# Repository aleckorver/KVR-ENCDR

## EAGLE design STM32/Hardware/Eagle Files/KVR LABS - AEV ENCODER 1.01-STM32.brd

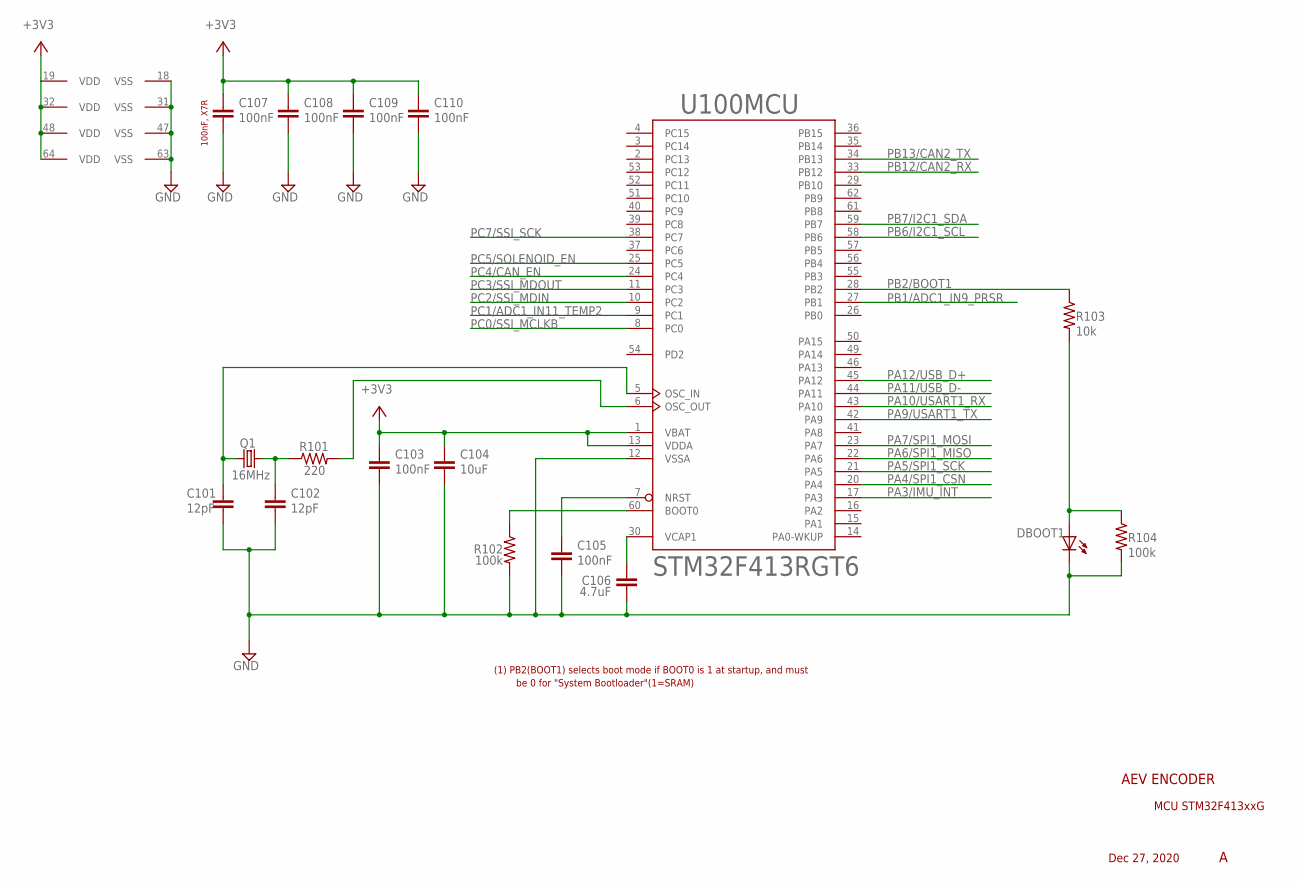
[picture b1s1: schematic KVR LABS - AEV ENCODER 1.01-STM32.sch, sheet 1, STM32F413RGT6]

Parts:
C101, C102: 12pF; C0603
C103, C105, C107, C108, C109, C110: 100nF; C0603
C104: 10uF; C0603
C106: 4.7uF; C0603
DBOOT1: LEDCHIPLED_0805; CHIPLED_0805
Q1: 16MHz; CRY3225-4
R101: 220; R0603
R102, R104: 100k; R0603
R103: 10k; R0603
U100: STM32F413RGT6; LQFP64_STMLIB

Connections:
+3V3: C103.1, C104.1, C107.1, C108.1, C109.1, C110.1, U100.1 (VBAT), U100.13 (VDDA), U100.19 (VDD), U100.32 (VDD), U100.48 (VDD), U100.64 (VDD); also elsewhere on the board
BOOT0: R102.1, U100.60 (BOOT0); also elsewhere on the board
GND: C101.2, C102.2, C103.2, C104.2, C105.2, C106.2, C107.2, C108.2, C109.2, C110.2, DBOOT1.C, R102.2, R104.2, U100.12 (VSSA), U100.18 (VSS), U100.31 (VSS), U100.47 (VSS), U100.63 (VSS); also elsewhere on the board
unnamed: DBOOT1.A, R103.2, R104.1
unnamed: R101.2, U100.6 (OSC_OUT)
NRST: C105.1, U100.7 (NRST)
OSC_IN: C101.1, Q1.3 (2), U100.5 (OSC_IN)
OSC_OUT: C102.1, Q1.1, R101.1
PA3/IMU_INT: U100.17 (PA3); also elsewhere on the board
PA4/SPI1_CSN: U100.20 (PA4); also elsewhere on the board
PA5/SPI1_SCK: U100.21 (PA5); also elsewhere on the board
PA6/SPI1_MISO: U100.22 (PA6); also elsewhere on the board
PA7/SPI1_MOSI: U100.23 (PA7); also elsewhere on the board
PA9/USART1_TX: U100.42 (PA9); also elsewhere on the board
PA10/USART1_RX: U100.43 (PA10); also elsewhere on the board
PA11/USB_D-: U100.44 (PA11); also elsewhere on the board
PA12/USB_D+: U100.45 (PA12); also elsewhere on the board
PB1/ADC1_IN9_PRSR: U100.27 (PB1); also elsewhere on the board
PB2/BOOT1: R103.1, U100.28 (PB2); also elsewhere on the board
PB6/I2C1_SCL: U100.58 (PB6)
PB7/I2C1_SDA: U100.59 (PB7)
PB12/CAN2_RX: U100.33 (PB12); also elsewhere on the board
PB13/CAN2_TX: U100.34 (PB13); also elsewhere on the board
PC0/SSI_MCLKB: U100.8 (PC0); also elsewhere on the board
PC1/ADC1_IN11_TEMP2: U100.9 (PC1); also elsewhere on the board
PC2/SSI_MDIN: U100.10 (PC2); also elsewhere on the board
PC3/SSI_MDOUT: U100.11 (PC3); also elsewhere on the board
PC4/CAN_EN: U100.24 (PC4); also elsewhere on the board
PC5/SOLENOID_EN: U100.25 (PC5); also elsewhere on the board
PC7/SSI_SCK: U100.38 (PC7); also elsewhere on the board
VCAP: C106.1, U100.30 (VCAP1)

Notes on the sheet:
AEV ENCODER
MCU STM32F413xxG
Dec 27, 2020
100nF, X7R
(1) PB2(BOOT1) selects boot mode if BOOT0 is 1 at startup, and must
be 0 for "System Bootloader"(1=SRAM)

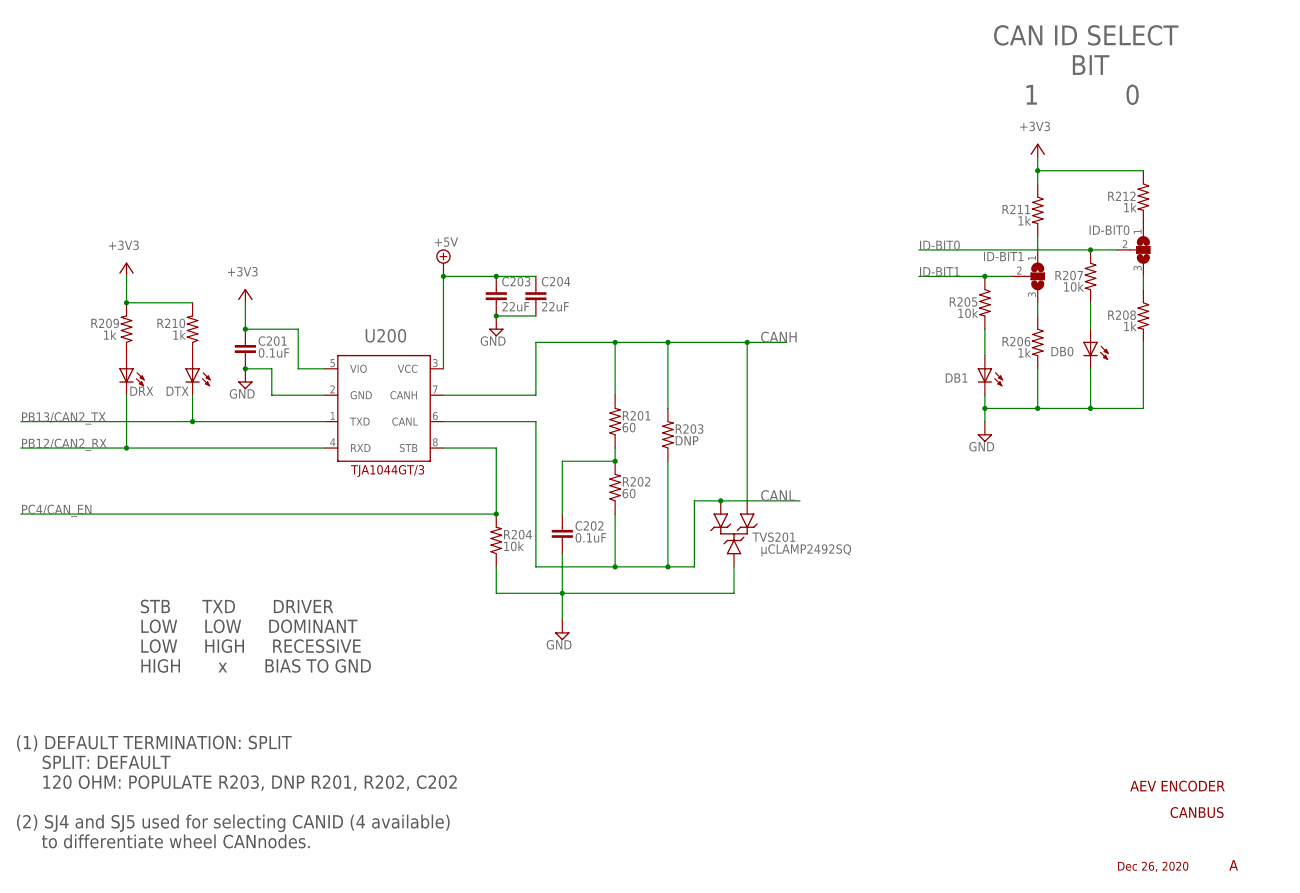
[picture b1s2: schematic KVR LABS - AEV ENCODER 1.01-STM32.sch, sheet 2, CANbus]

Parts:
C201, C202: 0.1uF; C0603
C203, C204: 22uF; C1206
D201: μCLAMP2492SQ; SOT-23_3L_ONS
DB0, DB1: LEDCHIPLED_0805; CHIPLED_0805
DRX: LEDCHIPLED_0805; CHIPLED_0805
DTX: LEDCHIPLED_0805; CHIPLED_0805
ID-BIT0, ID-BIT1: SJ2W; SJ_2
R201, R202: 60; R0603
R203: DNP; R0603
R204, R205, R207: 10k; R0603
R206, R208, R209, R210, R211, R212: 1k; R0603
U200: TJA1044GT/3; SO-8_S_LIT

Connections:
+3V3: C201.1, R209.2, R210.2, R211.1, R212.1, U200.5 (VIO); also elsewhere on the board
+5V: C203.1, C204.1, U200.3 (VCC); also elsewhere on the board
CANH: D201.2, R201.2, R203.2, U200.7 (CANH); also elsewhere on the board
CANL: D201.1, R202.1, R203.1, U200.6 (CANL); also elsewhere on the board
GND: C201.2, C202.2, C203.2, C204.2, D201.3, DB0.C, DB1.C, R204.1, R206.2, R208.2, U200.2 (GND); also elsewhere on the board
ID-BIT0: ID-BIT0.2, R207.1
ID-BIT1: ID-BIT1.2, R205.1
unnamed: ID-BIT1.3, R206.1
unnamed: ID-BIT0.3, R208.1
unnamed: DB0.A, R207.2
unnamed: DB1.A, R205.2
unnamed: ID-BIT1.1, R211.2
unnamed: ID-BIT0.1, R212.2
unnamed: DRX.A, R209.1
unnamed: DTX.A, R210.1
PB12/CAN2_RX: DRX.C, U200.4 (RXD); also elsewhere on the board
PB13/CAN2_TX: DTX.C, U200.1 (TXD); also elsewhere on the board
PC4/CAN_EN: R204.2, U200.8 (STB); also elsewhere on the board
SPLIT: C202.1, R201.1, R202.2

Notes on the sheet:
CANBUS
AEV ENCODER
Dec 26, 2020
(1) DEFAULT TERMINATION: SPLIT SPLIT: DEFAULT 120 OHM: POPULATE R203, DNP R201, R202, C202 (2) SJ4 and SJ5 used for selecting CANID (4 available) to differentiate wheel CANnodes.
CAN ID SELECT BIT 1 0
TVS201
U200
STB TXD DRIVER LOW LOW DOMINANT LOW HIGH RECESSIVE HIGH x BIAS TO GND

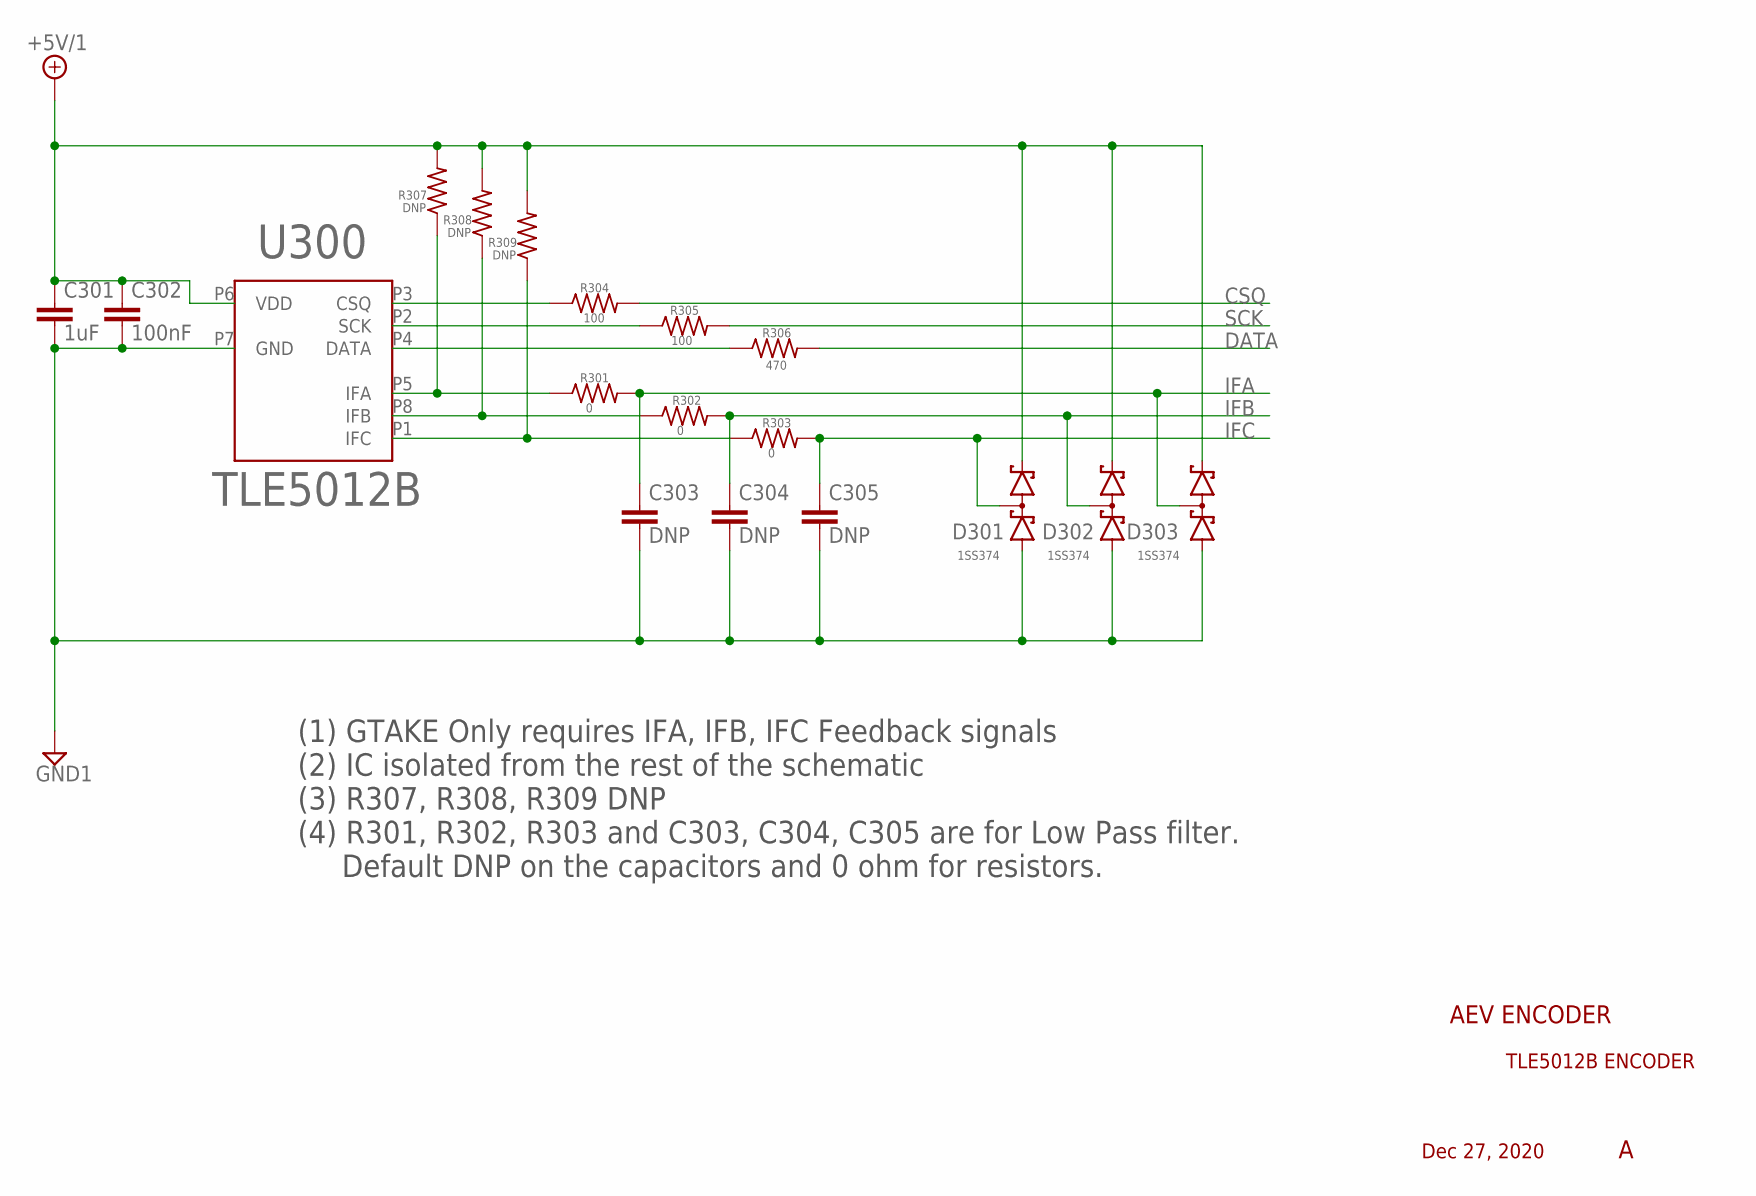
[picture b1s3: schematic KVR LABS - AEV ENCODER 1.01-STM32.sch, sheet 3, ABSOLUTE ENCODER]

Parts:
C301: 1uF; C0603
C302: 100nF; C0603
C303, C304, C305: DNP; C0603
D301, D302, D303: BAS70-04; SOT23
R301, R302, R303: 0; R0603
R304, R305: 100; R0603
R306: 470; R0603
R307, R308, R309: DNP; R0603
U300: TLE5012B; PG-DSO-8

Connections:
+5V/1: C301.1, C302.1, D301.2 (C2), D302.2 (C2), D303.2 (C2), R307.2, R308.2, R309.2, U300.P6 (VDD); also elsewhere on the board
CSQ: R304.2; also elsewhere on the board
DATA: R306.2; also elsewhere on the board
GND1: C301.2, C302.2, C303.2, C304.2, C305.2, D301.1 (A1), D302.1 (A1), D303.1 (A1), U300.P7 (GND); also elsewhere on the board
IFA: C303.1, D303.3 (C1A2), R301.2; also elsewhere on the board
IFB: C304.1, D302.3 (C1A2), R302.2; also elsewhere on the board
IFC: C305.1, D301.3 (C1A2), R303.2; also elsewhere on the board
unnamed: R304.1, U300.P3 (CSQ)
unnamed: R305.1, U300.P2 (SCK)
unnamed: R306.1, U300.P4 (DATA)
unnamed: R301.1, R307.1, U300.P5 (IFA)
unnamed: R302.1, R308.1, U300.P8 (IFB)
unnamed: R303.1, R309.1, U300.P1 (IFC)
SCK: R305.2; also elsewhere on the board

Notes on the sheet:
AEV ENCODER
TLE5012B ENCODER
Dec 27, 2020
U300
(1) GTAKE Only requires IFA, IFB, IFC Feedback signals (2) IC isolated from the rest of the schematic (3) R307, R308, R309 DNP (4) R301, R302, R303 and C303, C304, C305 are for Low Pass filter. Default DNP on the capacitors and 0 ohm for resistors.

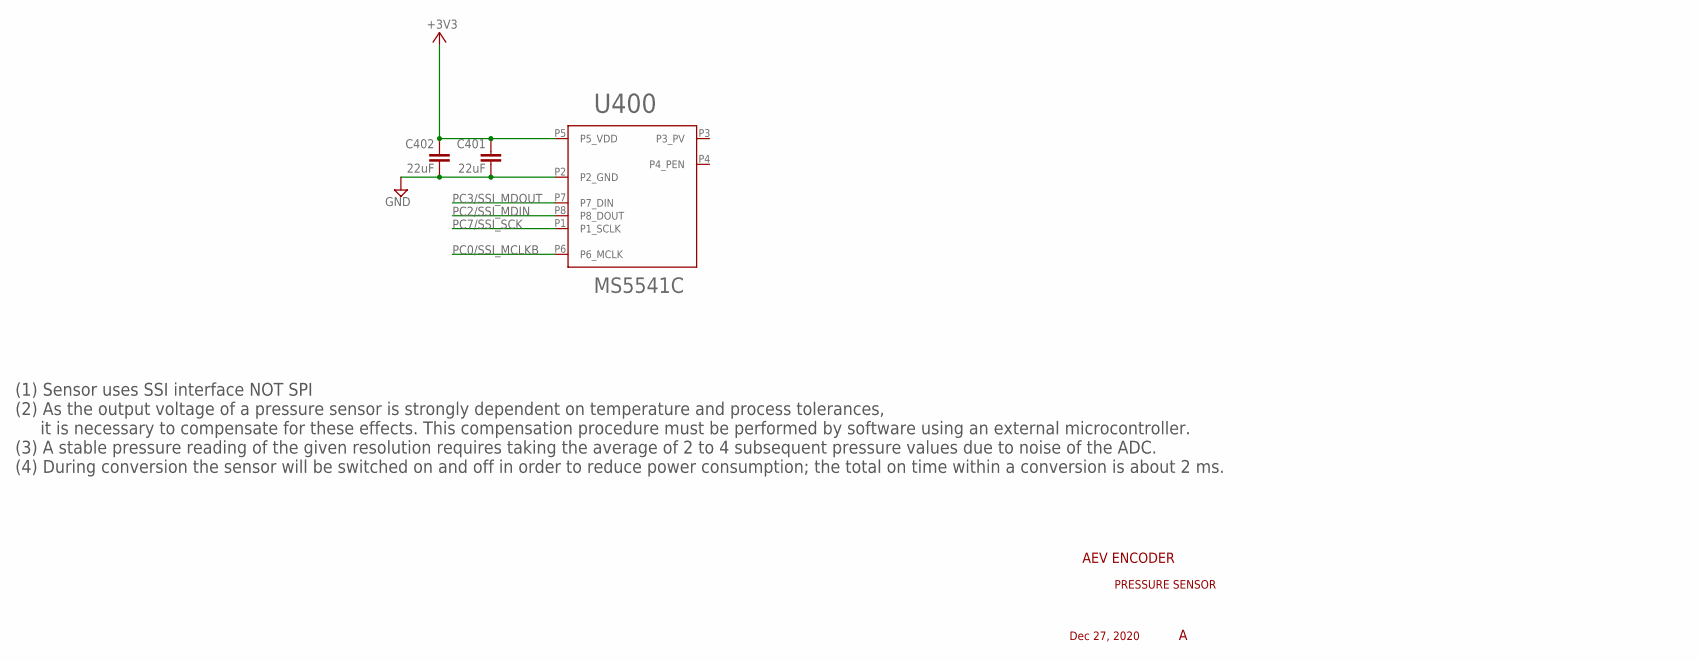
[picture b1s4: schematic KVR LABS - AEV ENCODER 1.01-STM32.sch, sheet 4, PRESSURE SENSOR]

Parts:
C401, C402: 22uF; C1206
U400: MS5541C

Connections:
+3V3: C401.1, C402.1, U400.P5 (P5_VDD); also elsewhere on the board
GND: C401.2, C402.2, U400.P2 (P2_GND); also elsewhere on the board
PC0/SSI_MCLKB: U400.P6 (P6_MCLK); also elsewhere on the board
PC2/SSI_MDIN: U400.P8 (P8_DOUT); also elsewhere on the board
PC3/SSI_MDOUT: U400.P7 (P7_DIN); also elsewhere on the board
PC7/SSI_SCK: U400.P1 (P1_SCLK); also elsewhere on the board

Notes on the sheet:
AEV ENCODER
PRESSURE SENSOR
Dec 27, 2020
(1) Sensor uses SSI interface NOT SPI (2) As the output voltage of a pressure sensor is strongly dependent on temperature and process tolerances, it is necessary to compensate for these effects. This compensation procedure must be performed by software using an external microcontroller. (3) A stabl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

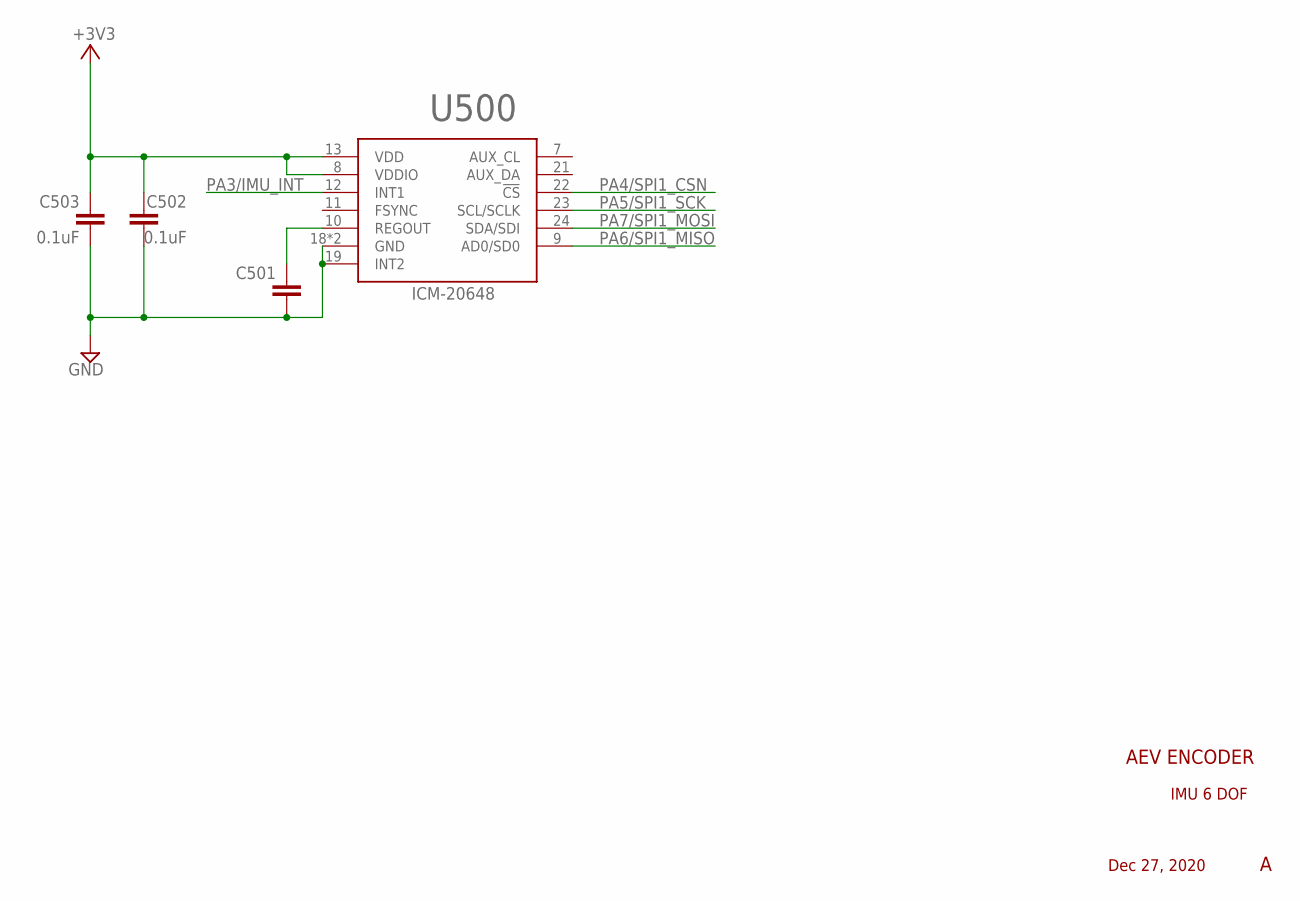
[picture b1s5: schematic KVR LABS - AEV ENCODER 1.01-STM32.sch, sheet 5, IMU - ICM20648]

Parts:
C501, C502, C503: 0.1uF; C0603
U500: ICM-20648

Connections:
+3V3: C502.1, C503.1, U500.8 (VDDIO), U500.13 (VDD); also elsewhere on the board
GND: C501.2, C502.2, C503.2, U500.18 (GND), U500.19 (INT2), U500.20 (GND); also elsewhere on the board
PA3/IMU_INT: U500.12 (INT1); also elsewhere on the board
PA4/SPI1_CSN: U500.22 (!CS); also elsewhere on the board
PA5/SPI1_SCK: U500.23 (SCL/SCLK); also elsewhere on the board
PA6/SPI1_MISO: U500.9 (AD0/SD0); also elsewhere on the board
PA7/SPI1_MOSI: U500.24 (SDA/SDI); also elsewhere on the board
REGOUT2: C501.1, U500.10 (REGOUT)

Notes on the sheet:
AEV ENCODER
IMU 6 DOF
Dec 27, 2020

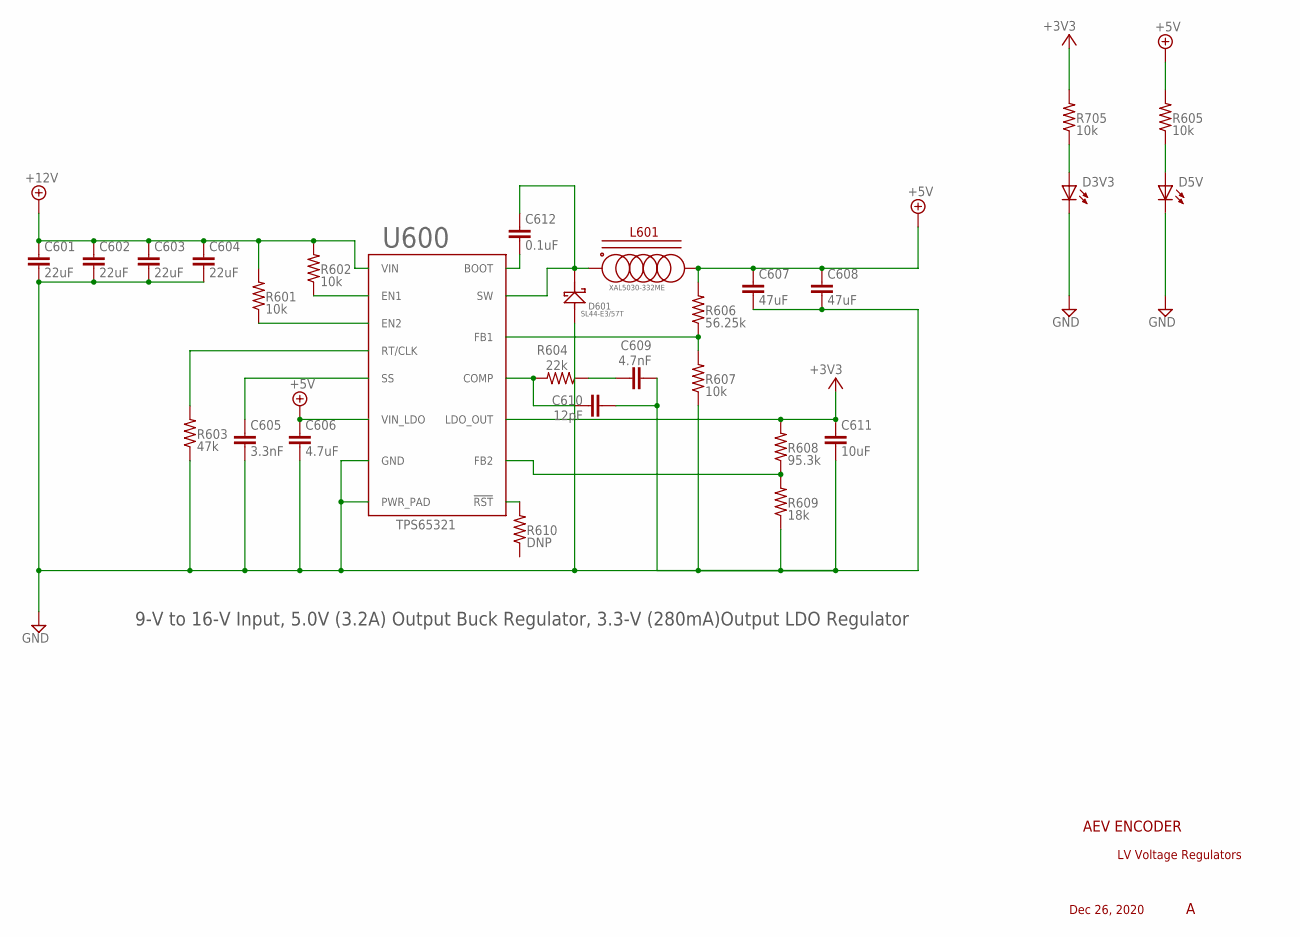
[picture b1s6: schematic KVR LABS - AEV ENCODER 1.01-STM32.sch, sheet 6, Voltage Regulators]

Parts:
C601, C602, C603, C604: 22uF; C0603
C605: 3.3nF; C0603
C606: 4.7uF; C0603
C607, C608: 47uF; C1210
C609: 4.7nF; C0603
C610: 12pF; C0603
C611: 10uF; C0603
C612: 0.1uF; C0603
D3V3, D5V: LEDCHIPLED_0805; CHIPLED_0805
D601: SL44; DO-214AB
L601: XAL5030
R601, R602, R605, R607, R705: 10k; R0603
R603: 47k; R0603
R604: 22k; R0603
R606: 56.25k; R0603
R608: 95.3k; R0603
R609: 18k; R0603
R610: DNP; R0603
U600: TPS65321-Q1; 14-HTSSOP

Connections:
+3V3: C611.1, R608.2, R705.2, U600.P4 (LDO_OUT); also elsewhere on the board
+5V: C606.1, C607.1, C608.1, L601.P2, R605.2, R606.2, U600.P3 (VIN_LDO); also elsewhere on the board
+12V: C601.1, C602.1, C603.1, C604.1, R601.2, R602.2, U600.P2 (VIN); also elsewhere on the board
BOOT: C612.2, U600.P1 (BOOT)
COMP: C610.1, R604.2, U600.P12 (COMP)
EN1: R602.1, U600.P8 (EN1)
EN2: R601.1, U600.P7 (EN2)
FB1: R606.1, R607.2, U600.P11 (FB1)
FB2: R608.1, R609.2, U600.P5 (FB2)
GND: C601.2, C602.2, C603.2, C604.2, C605.2, C606.2, C607.2, C608.2, C609.2, C610.2, C611.2, D3V3.C, D5V.C, D601.ANODE, R603.1, R607.1, R609.1, U600.P13 (GND), U600.P15 (PWR_PAD), U600.P16 (PWR_PAD), U600.P17 (PWR_PAD), U600.P18 (PWR_PAD), U600.P19 (PWR_PAD), U600.P20 (PWR_PAD), U600.P21 (PWR_PAD), U600.P22 (PWR_PAD), U600.P23 (PWR_PAD); also elsewhere on the board
unnamed: D3V3.A, R705.1
unnamed: D5V.A, R605.1
unnamed: C609.1, R604.1
unnamed: R610.2, U600.P6 (!RST)
RT/CLK: R603.2, U600.P9 (RT/CLK)
SS: C605.1, U600.P10 (SS)
SW: C612.1, D601.CATHODE, L601.P1, U600.P14 (SW)

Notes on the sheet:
AEV ENCODER
LV Voltage Regulators
9-V to 16-V Input, 5.0V (3.2A) Output Buck Regulator, 3.3-V (280mA)Output LDO Regulator
Dec 26, 2020

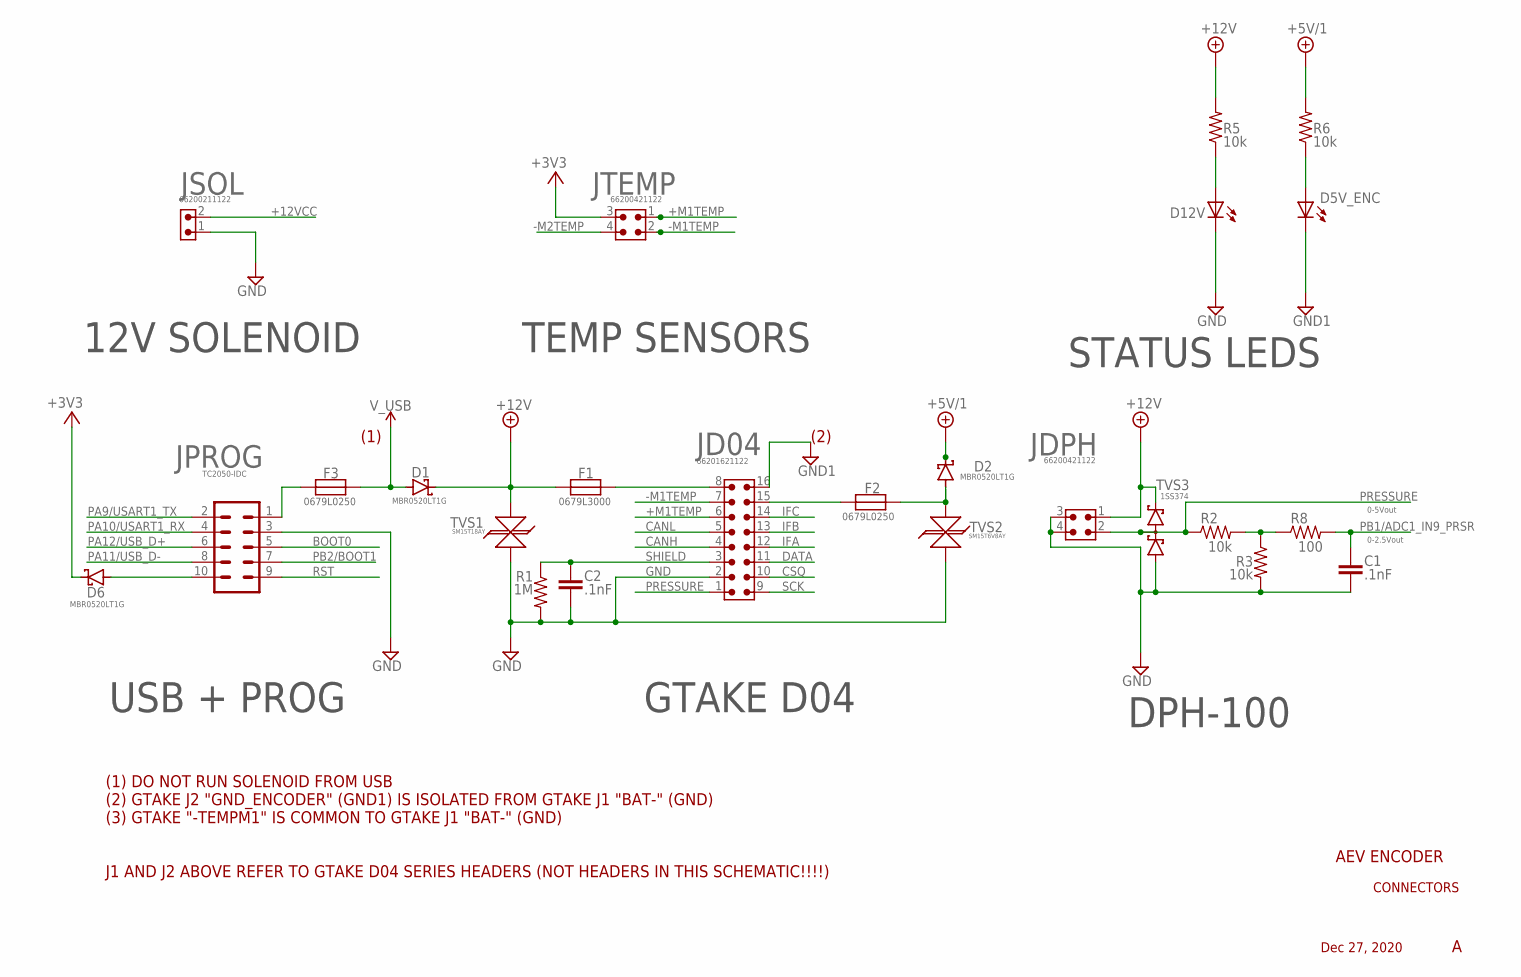
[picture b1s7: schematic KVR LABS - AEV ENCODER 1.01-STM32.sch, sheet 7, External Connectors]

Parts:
C1, C2: .1nF; C0603
D1, D2, D6: MBR0520LT1G; SODFL3718X115
D5V_ENC, D12V: LEDCHIPLED_0805; CHIPLED_0805
F1: 0679L3000; 2410(6125METRIC)
F2, F3: 0679L0250; 2410(6125METRIC)
JD04: 6620XX21122_66201621122; 66201621122
JDPH: 6620XX21122_66200421122; 66200421122
JPROG: TC2050-IDC
JSOL: 6620XX11122_66200211122; 66200211122
JTEMP: 6620XX21122_66200421122; 66200421122
R1: 1M; R0603
R2, R3, R5, R6: 10k; R0603
R8: 100; R0603
TVS1: SM15T18AY; SMC
TVS2: SM15T6V8AY; SMC
TVS3: BAS70-04; SOT23

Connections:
+3V3: D6.1 (C), JTEMP.3; also elsewhere on the board
+5V/1: D2.1 (C), R6.2; also elsewhere on the board
+12V: D1.1 (C), F1.P1, JDPH.1, R5.2, TVS1.P$2, TVS3.2 (C2); also elsewhere on the board
+12VCC: JSOL.2; also elsewhere on the board
+M1TEMP: JD04.6, JTEMP.1
-M1TEMP: JD04.7, JTEMP.2
-M2TEMP: JTEMP.4; also elsewhere on the board
BOOT0: JPROG.5; also elsewhere on the board
CANH: JD04.4; also elsewhere on the board
CANL: JD04.5; also elsewhere on the board
CSQ: JD04.10; also elsewhere on the board
DATA: JD04.11; also elsewhere on the board
GND: C1.2, C2.2, D12V.C, JD04.2, JDPH.3, JDPH.4, JPROG.3, JSOL.1, R1.2, R3.2, TVS1.P$1, TVS2.P$1, TVS3.1 (A1); also elsewhere on the board
GND1: D5V_ENC.C, JD04.16; also elsewhere on the board
IFA: JD04.12; also elsewhere on the board
IFB: JD04.13; also elsewhere on the board
IFC: JD04.14; also elsewhere on the board
unnamed: F2.P1, JD04.15
unnamed: D2.2 (A), F2.P2, TVS2.P$2
unnamed: F1.P2, JD04.8
unnamed: D6.2 (A), JPROG.10
unnamed: F3.P1, JPROG.1
unnamed: D12V.A, R5.1
unnamed: R2.2, R3.1, R8.1
unnamed: D5V_ENC.A, R6.1
PA9/USART1_TX: JPROG.2; also elsewhere on the board
PA10/USART1_RX: JPROG.4; also elsewhere on the board
PA11/USB_D-: JPROG.8; also elsewhere on the board
PA12/USB_D+: JPROG.6; also elsewhere on the board
PB1/ADC1_IN9_PRSR: C1.1, R8.2; also elsewhere on the board
PB2/BOOT1: JPROG.7; also elsewhere on the board
PRESSURE: JD04.1, JDPH.2, R2.1, TVS3.3 (C1A2)
RST: JPROG.9
SCK: JD04.9; also elsewhere on the board
SHIELD: C2.1, JD04.3, R1.1
V_USB: D1.2 (A), F3.P2

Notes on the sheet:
USB + PROG
0-5Vout
AEV ENCODER
Dec 27, 2020
GTAKE D04
DPH-100
TEMP SENSORS
12V SOLENOID
0-2.5Vout
STATUS LEDS
CONNECTORS
SM15T18AY
SM15T6V8AY
(1) DO NOT RUN SOLENOID FROM USB (2) GTAKE J2 "GND_ENCODER" (GND1) IS ISOLATED FROM GTAKE J1 "BAT-" (GND) (3) GTAKE "-TEMPM1" IS COMMON TO GTAKE J1 "BAT-" (GND) J1 AND J2 ABOVE REFER TO GTAKE D04 SERIES HEADERS (NOT HEADERS IN THIS SCHEMATIC!!!!)
(1)
(2)

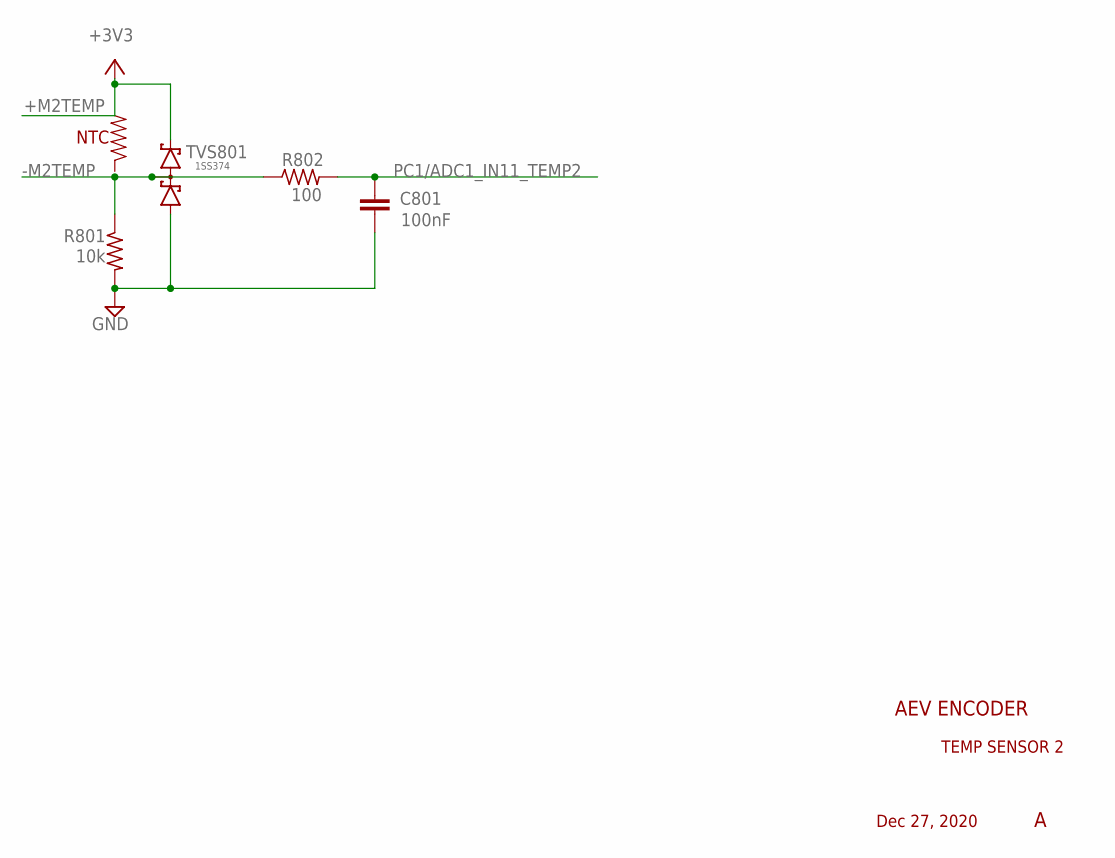
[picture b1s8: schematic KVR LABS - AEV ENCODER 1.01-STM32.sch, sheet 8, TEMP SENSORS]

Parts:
C801: 100nF; C0603
R801: 10k; R0603
R802: 100; R0603
TVS801: BAS70-04; SOT23

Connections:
+3V3: TVS801.2 (C2); also elsewhere on the board
-M2TEMP: R801.1, R802.1, TVS801.3 (C1A2); also elsewhere on the board
GND: C801.2, R801.2, TVS801.1 (A1); also elsewhere on the board
PC1/ADC1_IN11_TEMP2: C801.1, R802.2; also elsewhere on the board

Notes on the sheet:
NTC
+M2TEMP
AEV ENCODER
TEMP SENSOR 2
Dec 27, 2020

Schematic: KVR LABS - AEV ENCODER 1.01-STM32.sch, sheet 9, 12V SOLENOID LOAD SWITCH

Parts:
C901: 22uF; C1206
D901: MBR0520LT1G; SODFL3718X115
DSOL: LEDCHIPLED_0805; CHIPLED_0805
QN901: FDV305N; SOT323-3_NFET
QP901: ZXM61P02FTA; SOT323-3_NFET
R901, R902, R903: 10k; R0603

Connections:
+12V: C901.1, QP901.S, R901.2; also elsewhere on the board
+12VCC: D901.1 (C), QP901.D, R903.2; also elsewhere on the board
GND: C901.2, D901.2 (A), DSOL.C, QN901.S, R902.1; also elsewhere on the board
unnamed: QN901.D, QP901.G, R901.1
unnamed: DSOL.A, R903.1
PC5/SOLENOID_EN: QN901.G, R902.2; also elsewhere on the board

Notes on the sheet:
Voltage Max: 20V Current Cont: 4.2A (Ta) Current Pulse: 17A Max (<10uS)
AEV ENCODER
SOLENOID SWITCH
DEC 27, 2020
QP901
QN901

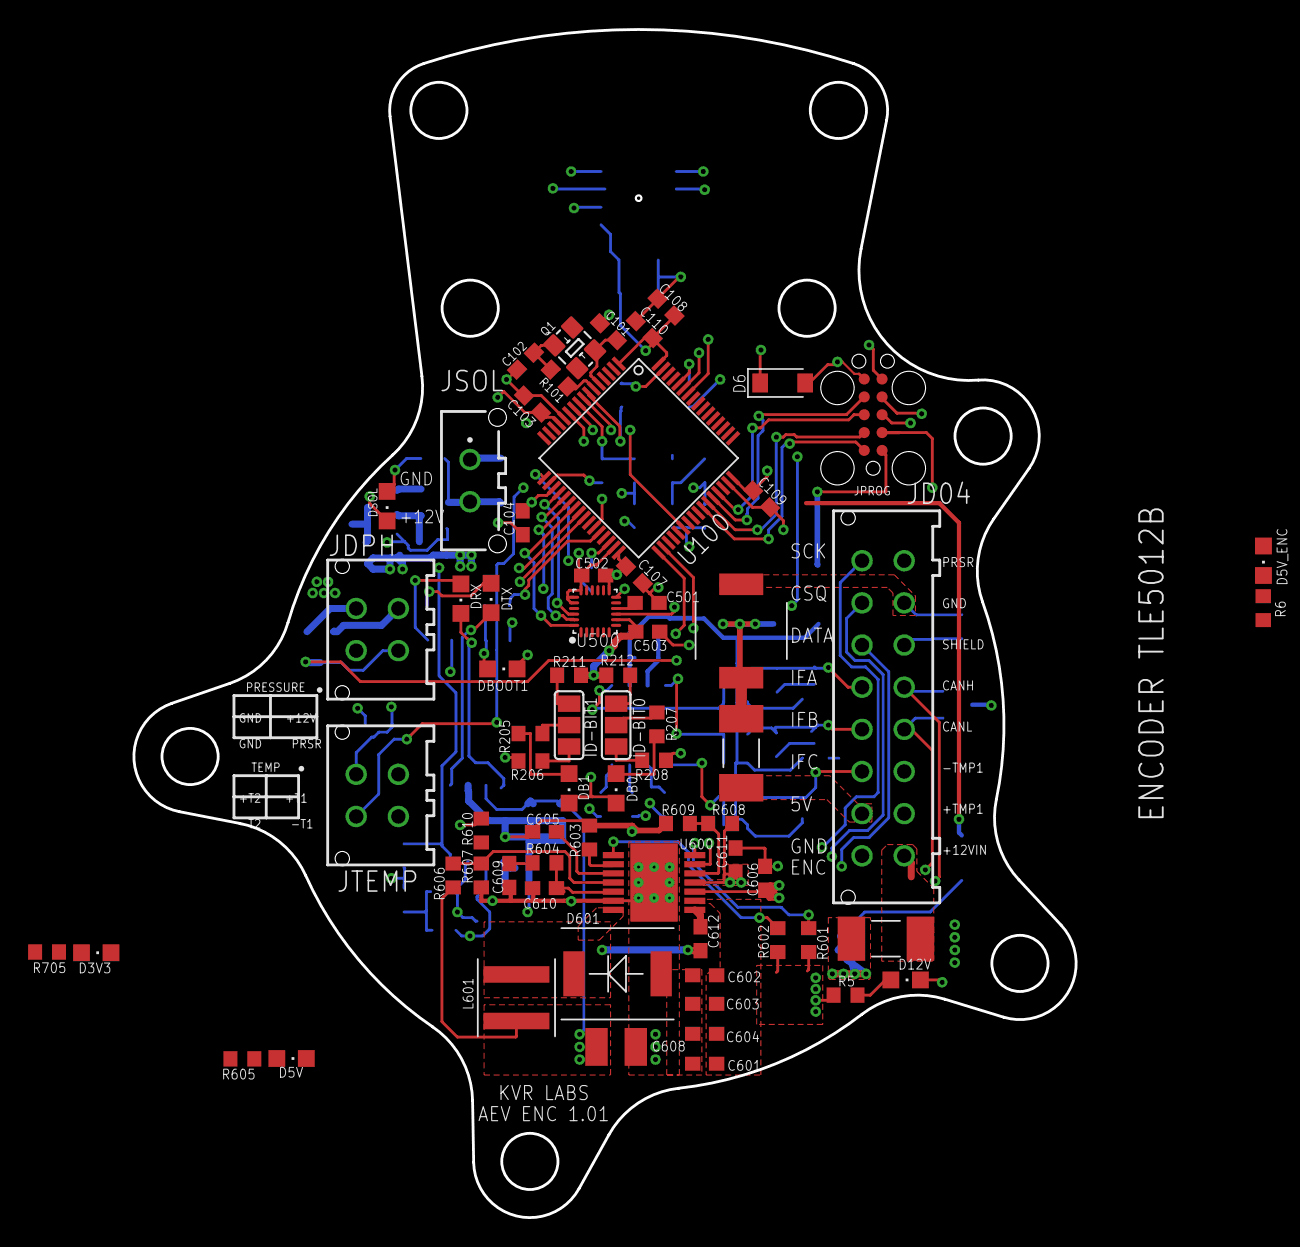
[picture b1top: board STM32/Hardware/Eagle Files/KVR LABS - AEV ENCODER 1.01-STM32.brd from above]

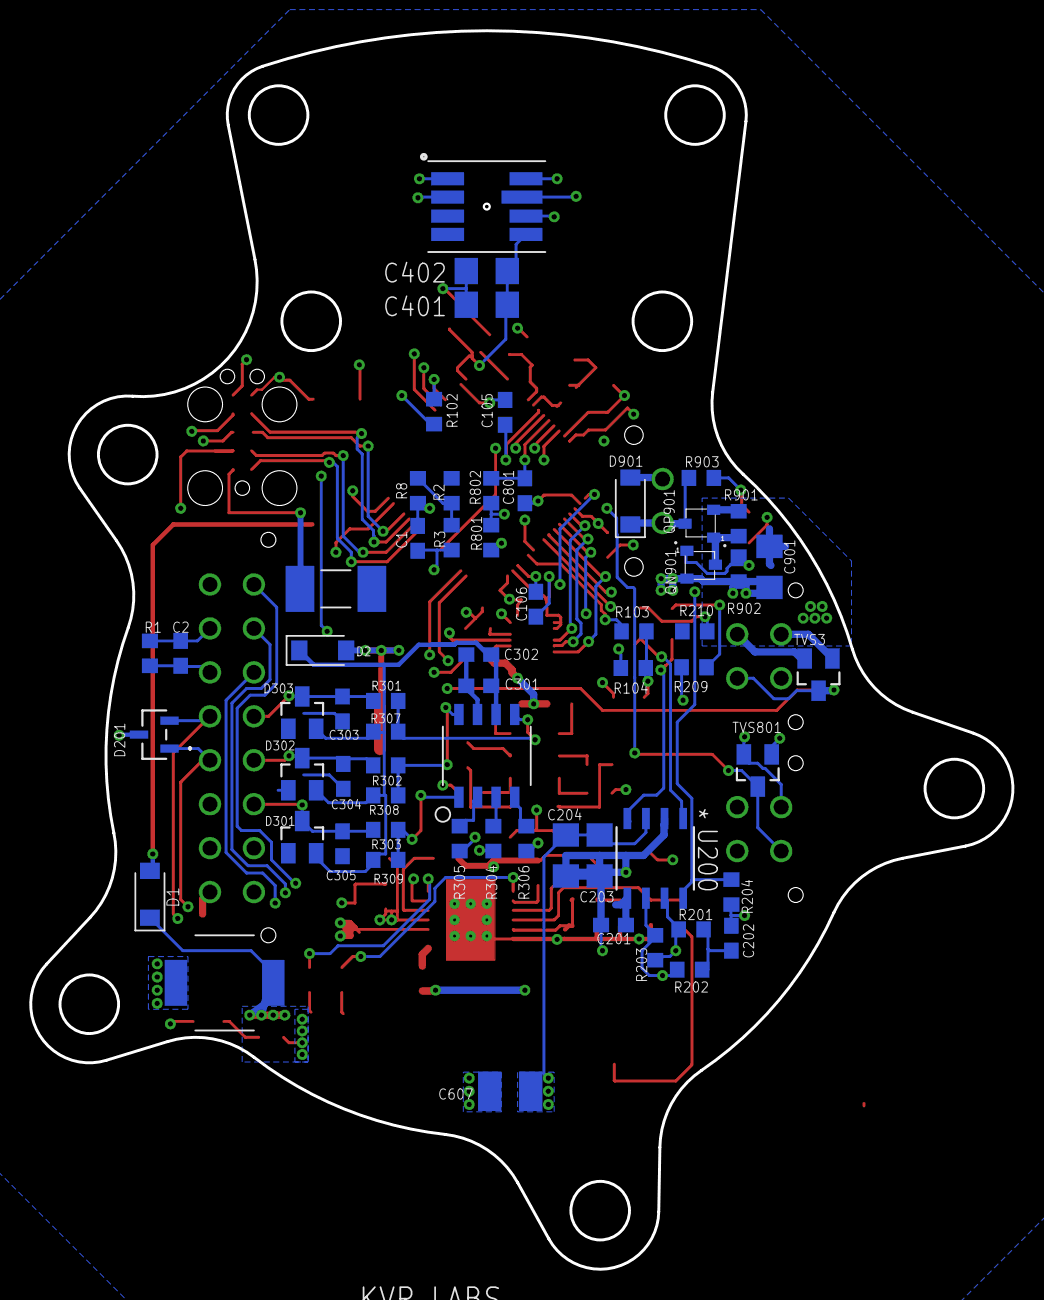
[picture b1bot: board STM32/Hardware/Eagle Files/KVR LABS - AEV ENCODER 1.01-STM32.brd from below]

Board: 4 copper layers, 67.1 x 84.6 mm, 130 parts (61 on the bottom side), 89 nets.

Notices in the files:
parts and their libraries:
Wurth_Connectors_WR-MPC3: Copyright: Würth Elektronik
SparkFun-PowerSymbols: Licensing: Creative Commons ShareAlike 4.0 International - https://creativecommons.org/licenses/by-sa/4.0
SparkFun: Licensing: CC v3.0 Share-Alike You are welcome to use this library for commercial purposes.
